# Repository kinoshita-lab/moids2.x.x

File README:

* About
These files are source codes for an artwork "moids 2.0".
You need at least arduino(pro, nano, duemilanove, etc.) or some alternatives to run this program.
We have confirmed this program works on aruduino-0015 version so far.

When you want to know more about moids, please visit our website
http://www.moids.org/

* Instructions
Being Arduino is not a comfortable developping environment for multiple sources, and the author has not arranged some scripts to do this task yet, you need to copy class libraries by hand every time you update sources.

1. Copy the 2 folders, "MsTimer2" , "Moids" to Arduino-****/hardware/libraries/
The destination is depends on where you have installed Arduino.

2. Start Arduino environment and open moids_arduino.pde, compile and upload to I/O board.

* Lisence
These source codes are completely public domain.
You can modify, distribute as you like.

---
Kinoshita-lab 2009

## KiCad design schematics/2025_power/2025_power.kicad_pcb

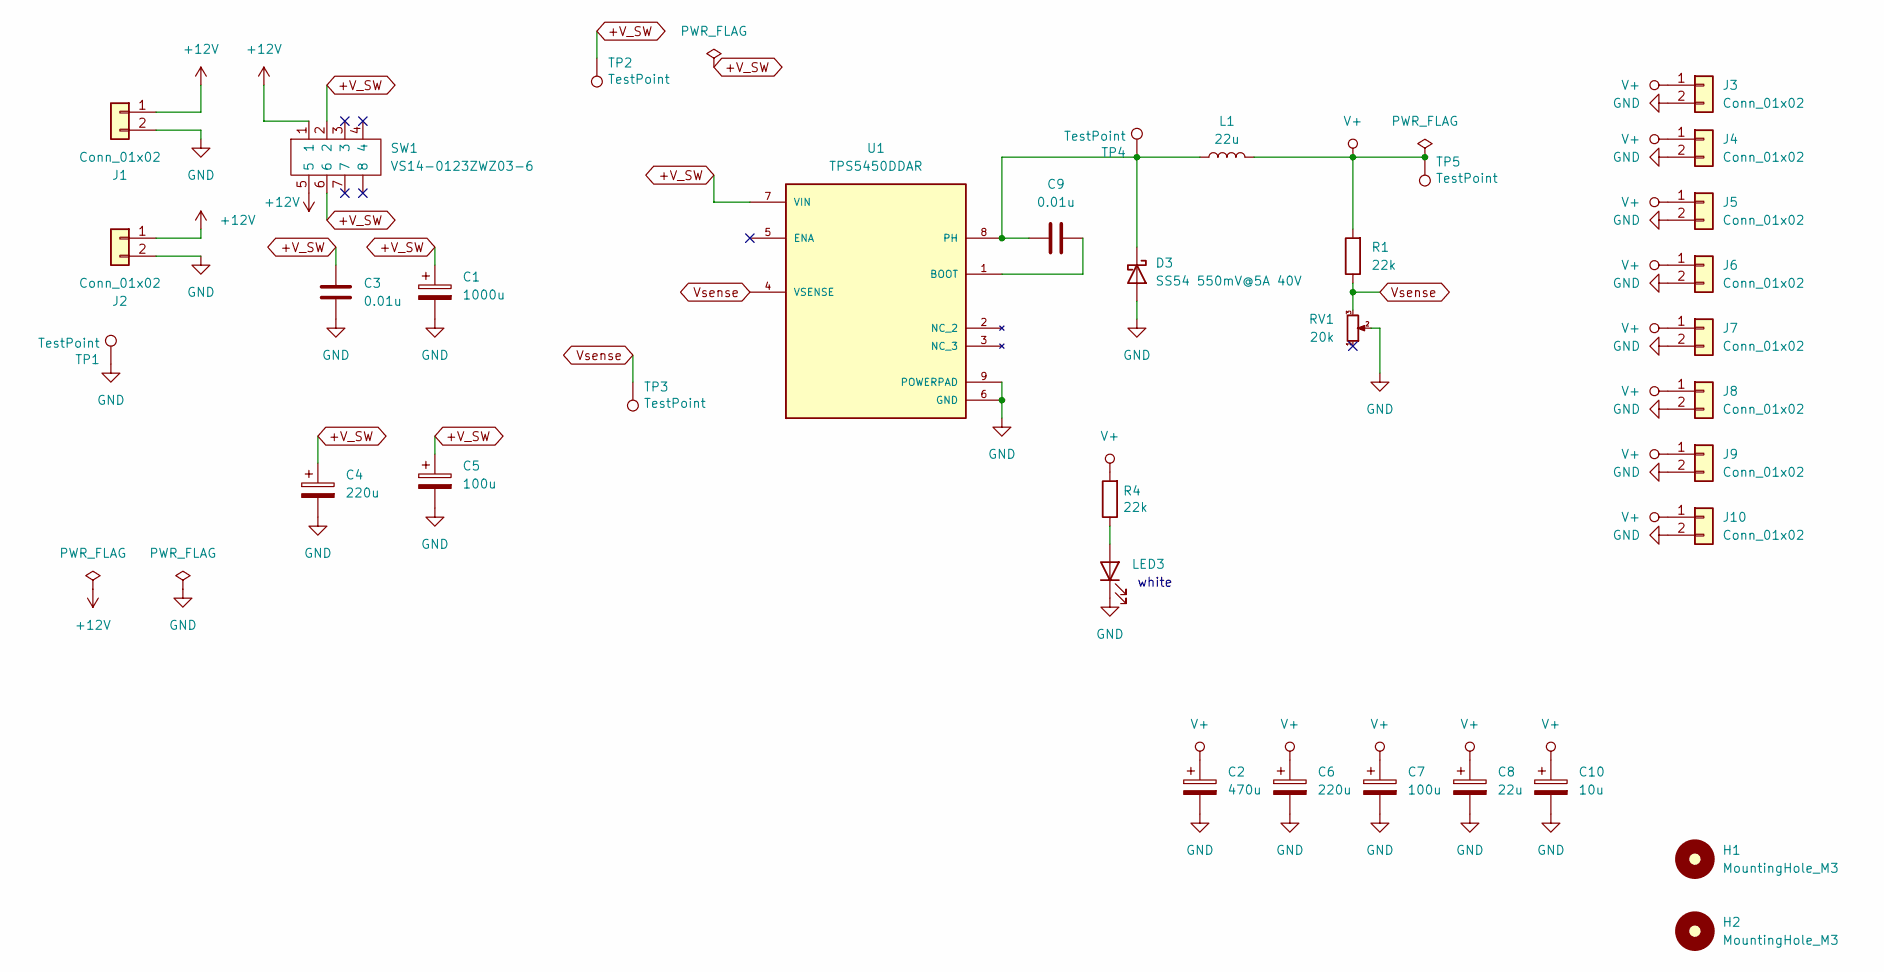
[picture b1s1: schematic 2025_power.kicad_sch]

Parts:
C1: 1000u; CP_Elec_10x10.5; LCSC C46550395
C2: 470u; CP_Elec_10x10; LCSC C3350
C3, C9: 0.01u; C0603; LCSC C57112
C4, C6: 220u; CP_Elec_6.3x7.7; LCSC C2918361
C5, C7: 100u; CP_Elec_6.3x7.7; LCSC C72478
C8: 22u; CP_Elec_6.3x5.4; LCSC C72505
C10: 10u; CP_Elec_4x5.4; LCSC C72485
D3: SS54 550mV@5A 40V; D_SMA; LCSC C727065
H1, H2: MountingHole_M3; MountingHole_3.2mm_M3
J1, J2: Conn_01x02; JST_VH_B2PS-VH_1x02_P3.96mm_Horizontal; LCSC C158007
J3, J4, J5, J6, J7, J8, J9, J10: Conn_01x02; JST_XH_B2B-XH-A_1x02_P2.50mm_Vertical; LCSC C158012
L1: 22u; Inductor_SMD_11.5x10.5; LCSC C22463844
LED3: 19-217/GHC-YR1S2/3T; LED_0603_1608Metric_Pad1.05x0.95mm_HandSolder; LCSC C2290
R1, R4: 22k; R_0402_1005Metric; LCSC C25547
RV1: 20k; Potentiometer_Bourns_3314J_Vertical; LCSC C55069
SW1: VS14-0123ZWZ03-6; Legion VS14-0123ZWZ03-6; LCSC C5186986
TP1, TP2, TP3, TP4, TP5: TestPoint; TP_1PAD
U1: TPS5450DDAR; CONV_TPS5450DDAR; PARTREV D; LCSC C114425

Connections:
+12V: J1.1, J2.1, SW1.1, SW1.5
+V_SW: C1.1, C3.2, C4.1, C5.1, SW1.2, SW1.6, TP2.1, U1.7 (VIN)
GND: C1.2, C2.2, C3.1, C4.2, C5.2, C6.2, C7.2, C8.2, C10.2, D3.2 (A), J1.2, J2.2, J3.2, J4.2, J5.2, J6.2, J7.2, J8.2, J9.2, J10.2, LED3.1 (K), RV1.2, TP1.1, U1.6 (GND), U1.9 (POWERPAD)
unnamed: C9.1, D3.1 (K), L1.1, TP4.1, U1.8 (PH)
unnamed: LED3.2 (A), R4.1
unnamed: C9.2, U1.1 (BOOT)
V+: C2.1, C6.1, C7.1, C8.1, C10.1, J3.1, J4.1, J5.1, J6.1, J7.1, J8.1, J9.1, J10.1, L1.2, R1.2, R4.2, TP5.1
Vsense: R1.1, RV1.3, TP3.1, U1.4 (VSENSE)

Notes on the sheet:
white

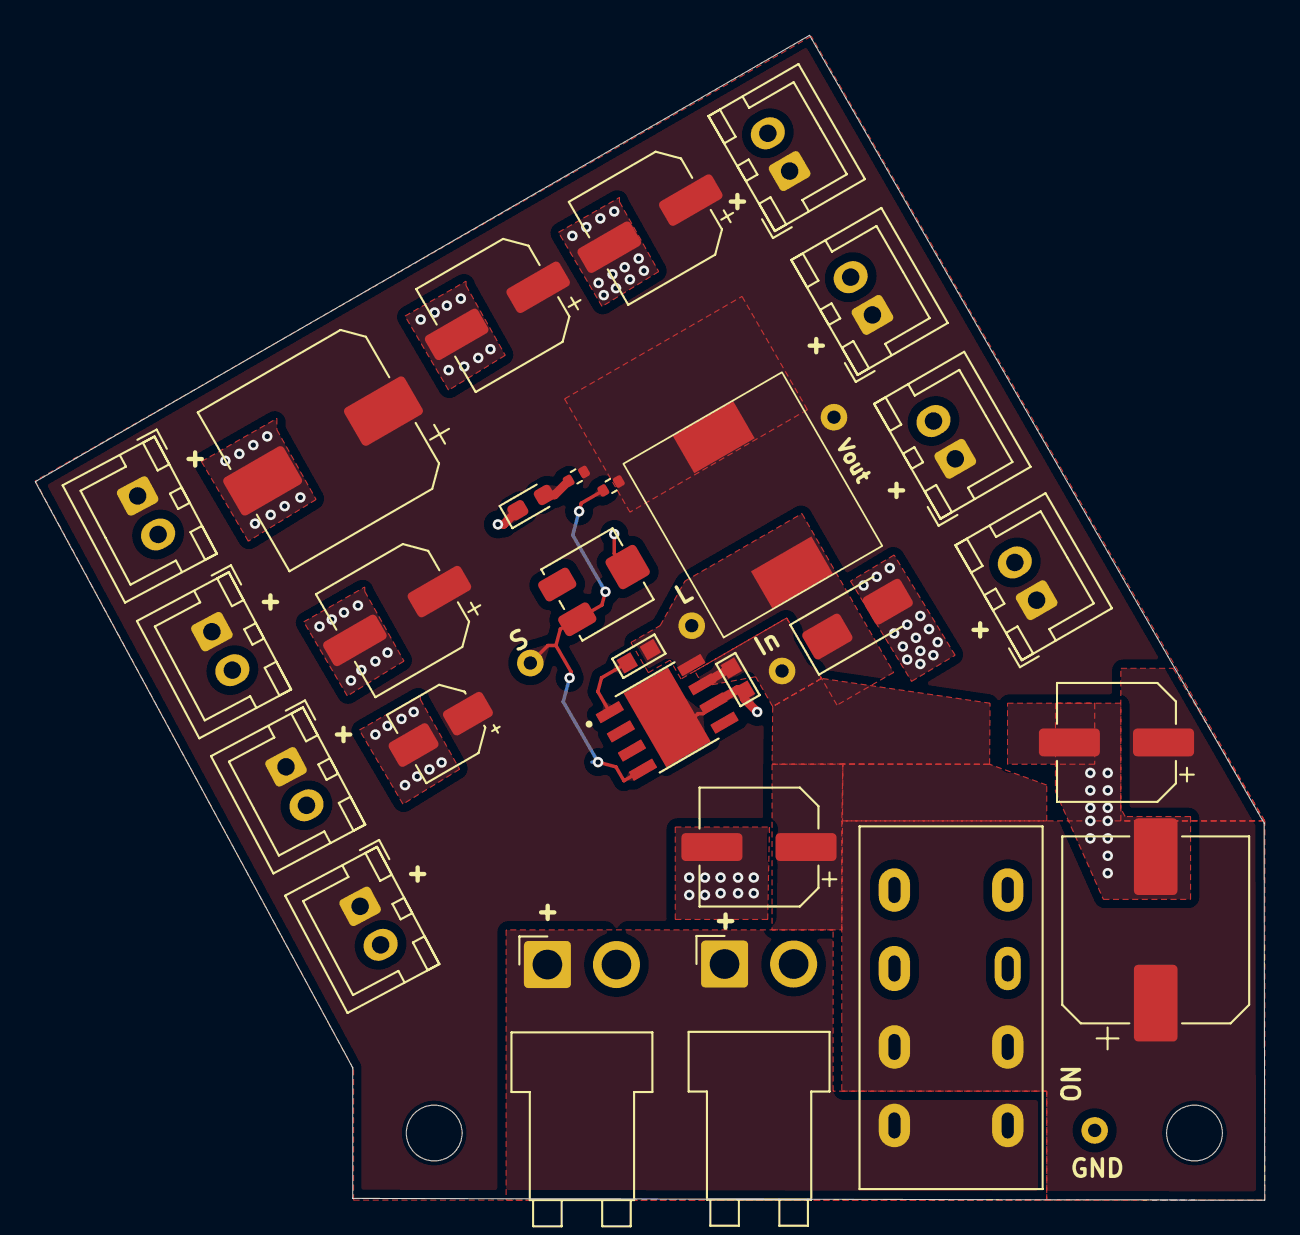
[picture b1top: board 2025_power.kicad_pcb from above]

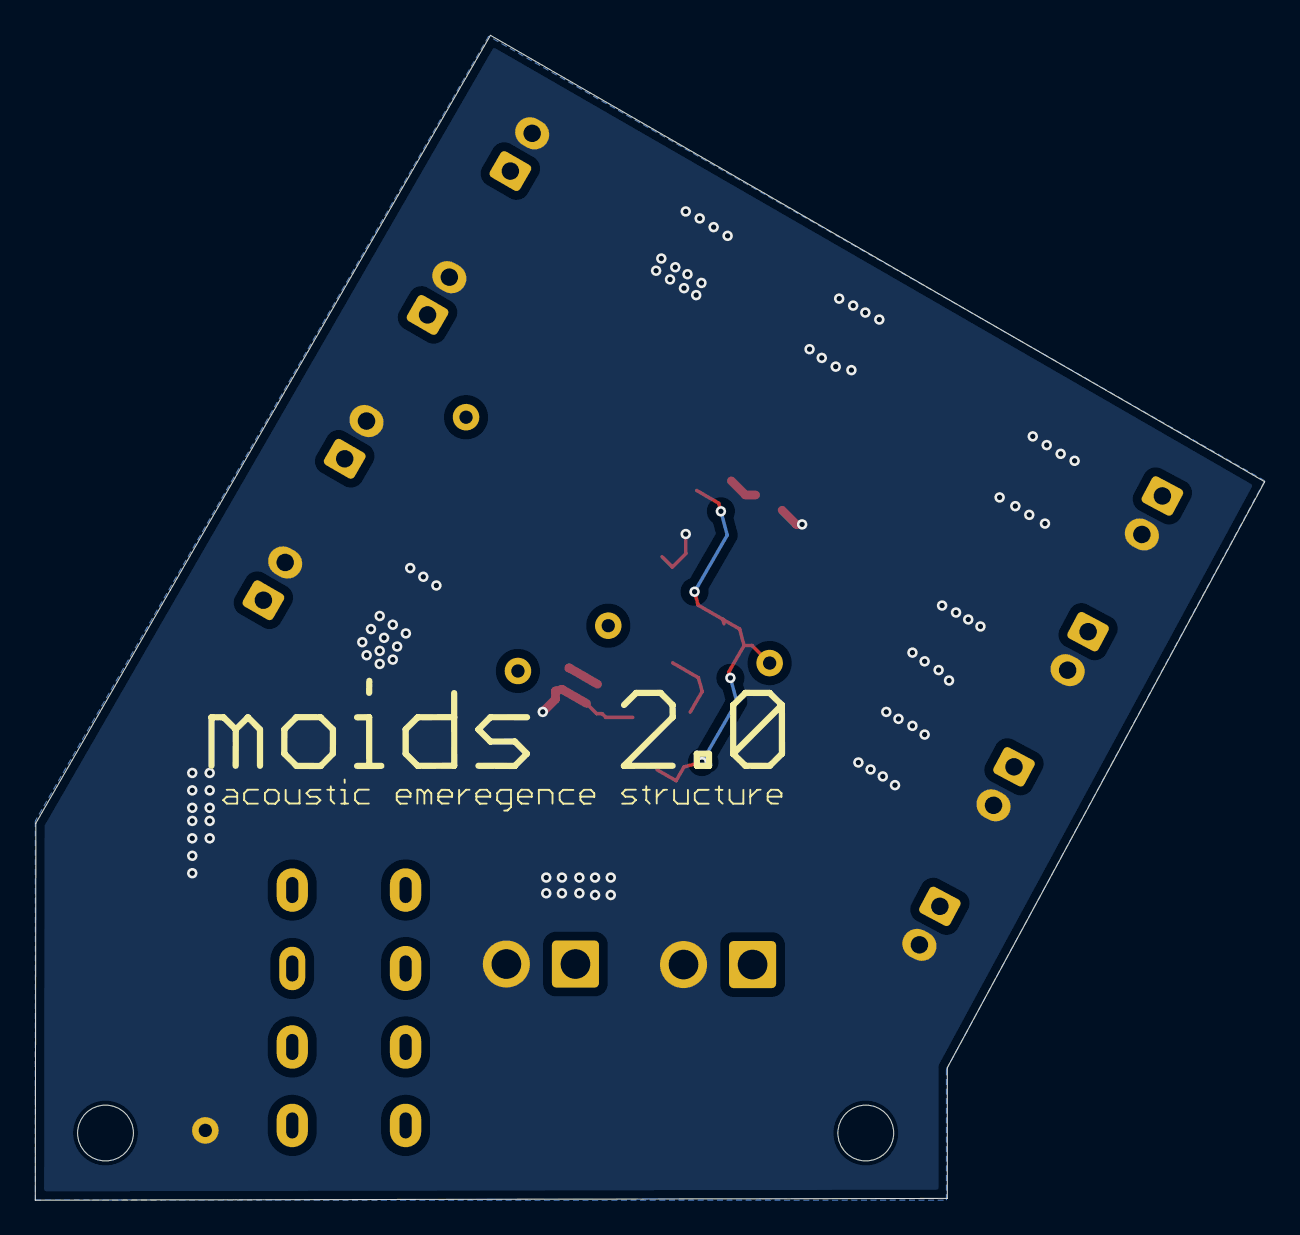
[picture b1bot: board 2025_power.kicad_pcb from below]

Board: 2 copper layers, 70.5 x 66.8 mm, 35 parts (3 on the bottom side), 8 nets.

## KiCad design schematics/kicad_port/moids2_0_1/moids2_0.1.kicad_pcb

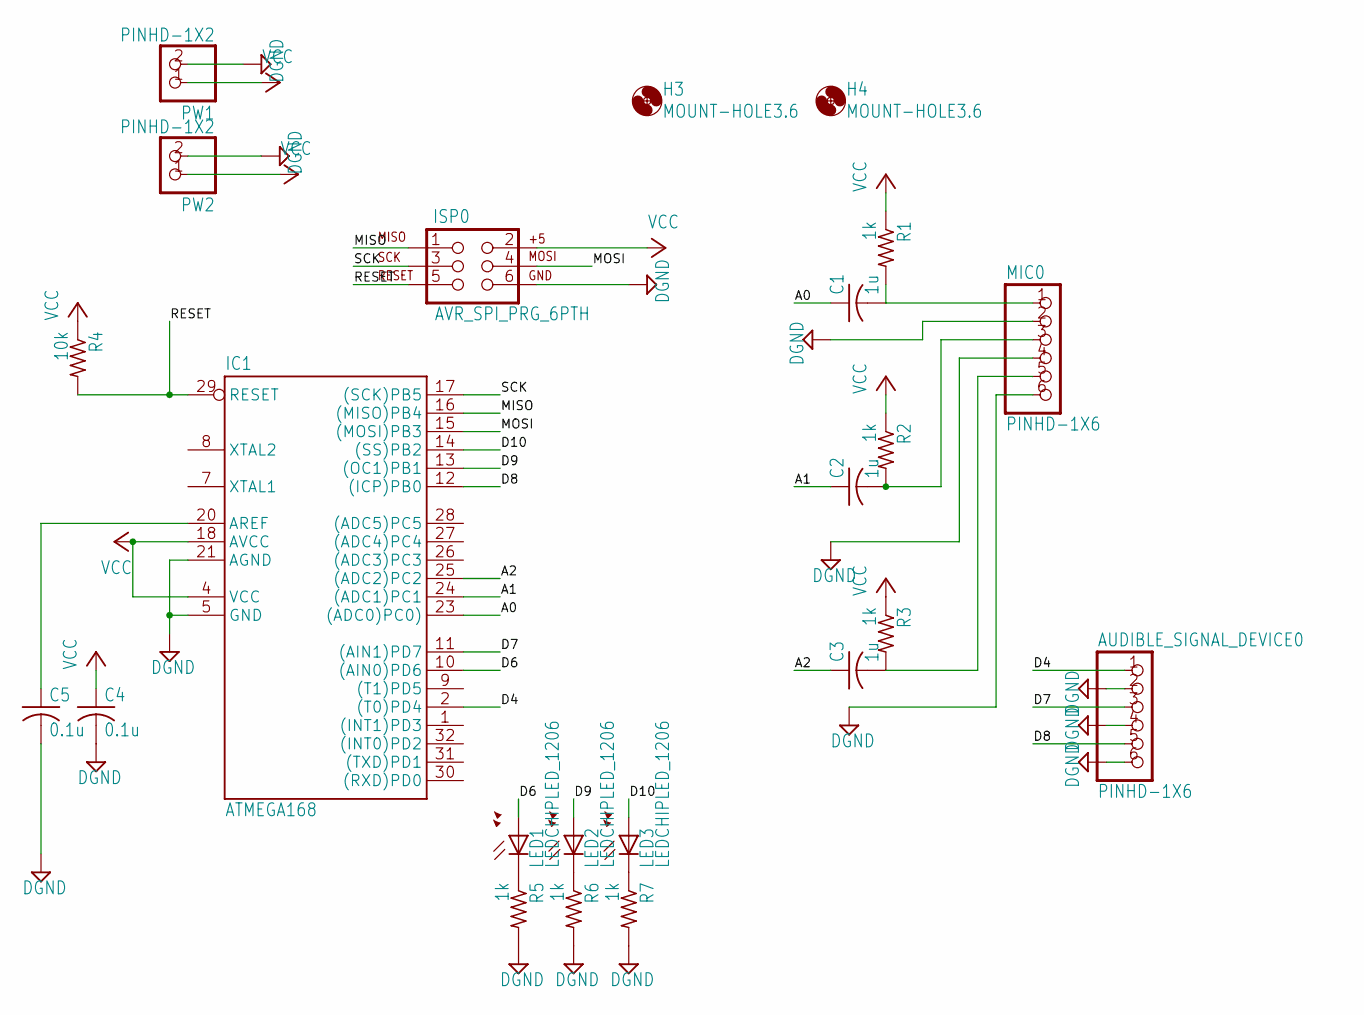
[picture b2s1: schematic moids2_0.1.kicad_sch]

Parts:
AUDIBLE_SIGNAL_DEVICE0: PINHD-1X6; 1X06
C1, C2, C3: 1u; C1005
C4, C5: 0.1u; C1005
H3, H4: MOUNT-HOLE3.6; 3,6
IC1: ATMEGA168; TQFP32-08
ISP0: AVR_SPI_PRG_6PTH; 2X3
LED1, LED2, LED3: LEDCHIPLED_1206; CHIPLED_1206
MIC0: PINHD-1X6; 1X06
PW1, PW2: PINHD-1X2; 1X02
R1, R2, R3, R5, R6, R7: 1k; R1005
R4: 10k; R1005

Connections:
A0: C1.1, IC1.23 ((ADC0)PC0))
A1: C2.1, IC1.24 ((ADC1)PC1)
A2: C3.1, IC1.25 ((ADC2)PC2)
AREF: C5.1, IC1.20 (AREF)
D4: AUDIBLE_SIGNAL_DEVICE0.1, IC1.2 ((T0)PD4)
D6: IC1.10 ((AIN0)PD6), LED1.A
D7: AUDIBLE_SIGNAL_DEVICE0.3, IC1.11 ((AIN1)PD7)
D8: AUDIBLE_SIGNAL_DEVICE0.5, IC1.12 ((ICP)PB0)
D9: IC1.13 ((OC1)PB1), LED2.A
D10: IC1.14 ((SS)PB2), LED3.A
DGND: AUDIBLE_SIGNAL_DEVICE0.2, AUDIBLE_SIGNAL_DEVICE0.4, AUDIBLE_SIGNAL_DEVICE0.6, C4.2, C5.2, IC1.5 (GND), IC1.21 (AGND), ISP0.6, MIC0.2, MIC0.4, MIC0.6, PW1.2, PW2.2, R5.2, R6.2, R7.2
MISO: IC1.16 ((MISO)PB4), ISP0.1
MOSI: IC1.15 ((MOSI)PB3), ISP0.4
unnamed: C1.2, MIC0.1, R1.2
unnamed: C2.2, MIC0.3, R2.2
unnamed: C3.2, MIC0.5, R3.2
unnamed: LED1.C, R5.1
unnamed: LED2.C, R6.1
unnamed: LED3.C, R7.1
RESET: IC1.29 (RESET), ISP0.5, R4.2
SCK: IC1.17 ((SCK)PB5), ISP0.3
VCC: C4.1, IC1.4 (VCC), IC1.18 (AVCC), ISP0.2, PW1.1, PW2.1, R1.1, R2.1, R3.1, R4.1

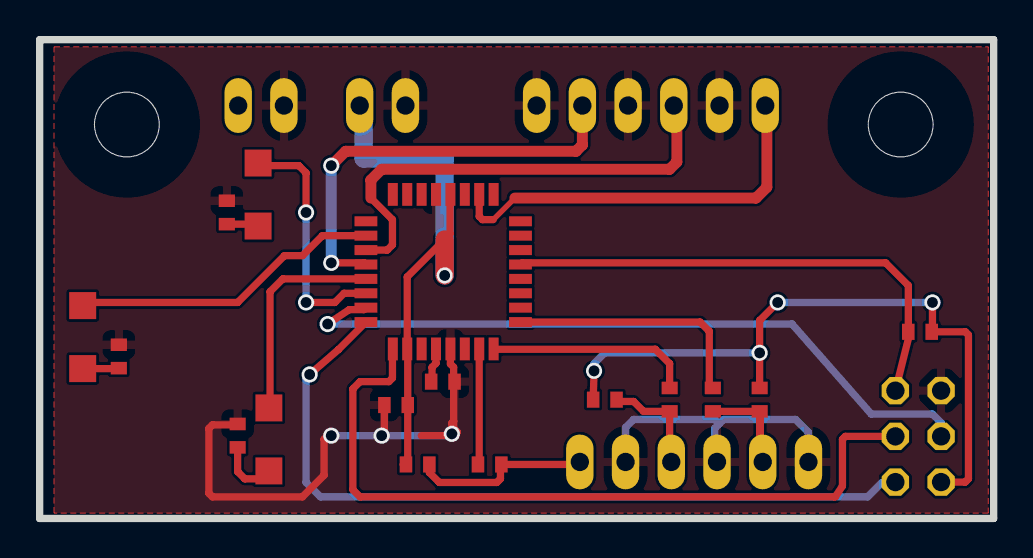
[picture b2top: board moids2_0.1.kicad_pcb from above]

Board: 2 copper layers, 53.0 x 26.6 mm, 23 parts (1 on the bottom side), 22 nets.

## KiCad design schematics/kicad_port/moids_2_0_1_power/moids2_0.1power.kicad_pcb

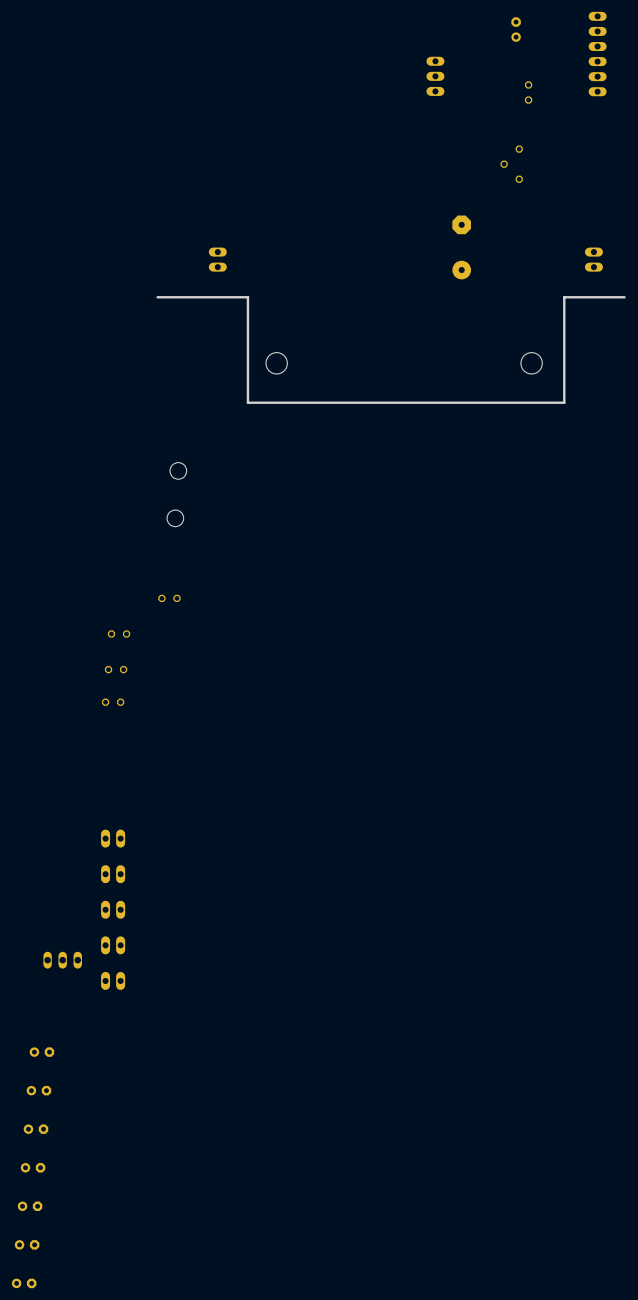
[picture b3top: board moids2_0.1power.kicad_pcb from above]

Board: 2 copper layers, 31 parts (0 on the bottom side), 7 nets, no tracks yet.

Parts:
C1: 0.1u; C025-024X044
C2, C3, C4, C5, C6, C7, C8, C9: 100u; E2,5-5
C10: 2200u; E7,5-16
H3, H4: MOUNT-HOLE3.6; 3,6
HEATSINKHOLE1, HEATSINKHOLE2: MOUNT-HOLE2.8; 2,8
IC1: LM338; 317TS
LED1: LED3MM
OUT1, OUT2, OUT3, OUT4, OUT5, OUT6, OUT7, OUT8: 1X02
PW1, PW2: 1X02
R1: 240; 0207_2V
R2: 500; B25P
R3: 300; 0207_2V
R4: 1k ~ 10k; 0207_2V
S1: TL32PO; TL3XPO

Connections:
DGND: C1.2, C2.-, C3.-, C4.-, C5.-, C6.-, C7.-, C8.-, C9.-, C10.-, LED1.K, OUT1.1, OUT2.1, OUT3.1, OUT4.1, OUT5.1, OUT6.1, OUT7.1, OUT8.1, PW1.1, PW2.1, R3.1
unnamed: IC1.1, R1.1, R2.S
unnamed: R2.A, R3.2
unnamed: LED1.A, R4.1
VCC: C10.+, PW1.2, PW2.2, S1.3
VIN: C1.1, IC1.3, R1.2, S1.2
VOUT: C2.+, C3.+, C4.+, C5.+, C6.+, C7.+, C8.+, C9.+, IC1.2, OUT1.2, OUT2.2, OUT3.2, OUT4.2, OUT5.2, OUT6.2, OUT7.2, OUT8.2, R4.2

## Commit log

2009-02-17 add main file
2009-02-17 add contents of moids-app(initial implementation)
2009-02-17 add README contents
2009-02-17 github generated gh-pages branch
2009-02-24 add UsTimer2
2009-02-24 remove cpp
2009-02-24 add pde
2009-02-24 added Makefile(saita specific configurations)
2009-02-24 modified pde
2009-05-30 removed ustimer
2009-05-30 add modified MsTimer2
2009-05-30 add moids class
2009-05-30 removed some files...
2009-05-30 modis 2.0 at coded culture version
2009-05-30 add README
2009-05-30 modified README, add instructions, lisence, etc.
2009-05-30 add schematics and board file
2009-05-31 add metalframe pdf made by mhrs
2010-07-17 reduce wait when moids state for yamaguchi 2009
2011-03-05 [schematics]fork moid2_0.1 to make power source schem
2011-03-05 [schematics]made a schem for power source
2011-03-06 [schematics]correct errors, made Power PCB
2011-03-09 [schematics][power]new layout
2011-03-09 [schematics][power]made pcb again
2011-03-22 [schematics][power]mhrs modified version
2011-03-23 [schematics][power]mhrs modified version(correct gnd plane version)
2011-03-23 [schematics][power]correct DRC Check
2011-03-23 [schematics][power]create P-ban garbar data based on http://www.p-ban.com/gerber/eagle.html
2012-01-28 add power schematics and pcb
2012-01-28 add TODO file
2012-01-28 update TODO
2012-01-29 modify folder structure, modify some files for Arduino 1.0
2012-01-29 remove pde file (use ino file)
2012-02-05 format sources
2012-02-05 add random sound table(not yet connected to working programs)
2012-02-05 rename README to make it markdown format
2012-02-05 modify README
2012-02-05 modify README.md again
2012-02-09 modified program for 2.0.3 least specification. varies sound on moids state.
2012-02-11 for 2.2.0 sounding experiment
2012-02-11 free osc mode
2012-03-07 2.0.3 for ZKM
2012-03-08 modify README and TODO, delete non-ascii files, add pdfs for schematics
2012-03-08 add manufacturing instruction
2012-08-19 rename MsTimer2, modifie some files for ease of tweaking(not completed)
2012-08-19 input audio double check feature can be tweaked
2012-08-19 add hex file. its configuration is ATMega168, 8MHz
2012-09-06 undo modification, original spec
2013-01-17 add power and light control feature
2019-07-11 add board
2019-07-11 add power board pdf
2025-11-14 obsolete and move old eagle files
2025-11-14 convert to the latest(and last?) eagle project
2025-11-14 convert latest eagle file to kicad
2025-11-14 add power source 2025(WIP)
2025-11-14 reorganize shchematics folder
2025-11-14 preserve original hex for revising in 2025
2025-11-14 WIP: compile available with arduino 2025(NOT WORKING!)
2025-11-15 WIP, debugging
2025-11-16 update software, confirm working! correct wrong timer counter max for 1sec
2025-11-16 remove test codes
2025-11-16 WIP: directly enter interactive
2025-11-16 directly enter interactive
2025-11-16 remove TOO BIG threshold
2025-11-16 WIP: reducing functions to detect issue
2025-11-17 make moids working only one
2025-11-17 WIP: make timer tick 10 times slower. seems working
2025-11-18 Add extra delay time to meet original specification
2025-11-18 introduce default argment to make void Moids::makeOffset more flexible
2025-11-18 make sampling period constant(125us)
2025-11-18 WIP: 20251118 camp
2025-12-27 2025 power revised
2026-02-04 [wip] remove delay_us
2026-02-05 apply clang-format formatting and refactor code
2026-02-05 [WIP] 20260205 working
2026-02-06 [WIP] remove unpredictable timer behavior
2026-02-06 [RELEASE] 20260206
